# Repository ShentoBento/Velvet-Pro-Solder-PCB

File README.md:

# Velvet Pro Solder PCB

A solder PCB designed to fit the Velvet Pro keyboard by Ampersandy.

Firmware: https://github.com/ShentoBento/Velvet-Pro-PCB-Firmware

---

## Specs

- Solder
- MCU: STM32F072CBTx
- JST SH 4-pin connector (for C3 Unified Daughterboards)
- Fixed ANSI enter
- Fixed 7u bottom row
- Fixed split right shift
- Stepped or full caps lock
- Split or full backspace
- VIA and Vial compatible (via the firmware linked above)

---

## Requirements

- **KiCad 10** or newer. Earlier versions will not open these files.
- Nothing else. All symbols, footprints, and 3D models used by this project are
  included in this repo — no external libraries to install, no PCM packages,
  no library paths to configure.

---

## Opening the project

1. Clone or download this repo.
2. Open `VP_Solder_KiCad/VP_Solder.kicad_pro` in KiCad.

The library paths are stored relative to the project folder, so the repo works
from any location on any operating system. If KiCad reports missing symbols or
footprints, the most likely cause is that the `shentobento_kicad_library/`
folder was not cloned alongside `VP_Solder_KiCad/`.

---

## What's in this repo

### `VP_Solder_KiCad/`

The KiCad project. These are the files you edit.

| File | What it is |
|---|---|
| `VP_Solder.kicad_pro` | Project file — **open this one** |
| `VP_Solder.kicad_sch` | Schematic |
| `VP_Solder.kicad_pcb` | Board layout |
| `fp-lib-table`, `sym-lib-table` | Point KiCad at the bundled library |
| `fabrication-toolkit-options.json` | Settings for the JLCPCB fabrication plugin |

### `VP_Solder_KiCad/production/`

Ready-to-order manufacturing files, generated with the JLCPCB Fabrication Toolkit plugin.

| File | Upload it to |
|---|---|
| `VP_Solder.zip` | JLCPCB's gerber upload — this is the board itself |
| `bom.csv` | Assembly service (which parts) |
| `positions.csv` | Assembly service (where they go) |

If you modify the design, **regenerate these** rather than reusing them. Stale
production files that don't match the current board are how wrong PCBs get
manufactured.

### `shentobento_kicad_library/`

Every symbol and footprint this project uses, in one place.

- `shentobento.kicad_sym` — all symbols
- `shentobento.pretty/` — all footprints
- `3dmodels/` — 3D models for the parts that need them

Symbols come with their footprints pre-assigned, so dragging a part into a
schematic gives you a working part with no footprint assignment step.

This folder is self-contained and can be copied into other keyboard projects.

### `reference files and images`

Not needed to build the board — useful if you're modifying the layout.

- `Plate_File_No_Flex_Cuts.dxf` / `Plate_File_with_Flex_Cuts.dxf` — the official
  Velvet Pro plate files, used to align switch and stabilizer positions
- `VP PCB DXF.dxf` — the official board outline, thanks to Andykit
- Various images of the PCB and schematic

---

## Credits and licenses

Keyboard footprints and symbols are derived from
[marbastlib](https://github.com/ebastler/marbastlib) by ebastler, licensed under
CERN-OHL-P v2. See `shentobento_kicad_library/LICENSE-marbastlib.txt`.

Generic footprints (passives, SOT-23, LQFP-48, JST SH, test points) are copied
from the KiCad standard libraries.

Modifications made to third-party files are recorded in
`shentobento_kicad_library/NOTICE.md`.

The Velvet Pro case and plate files are the work of Ampersandy.

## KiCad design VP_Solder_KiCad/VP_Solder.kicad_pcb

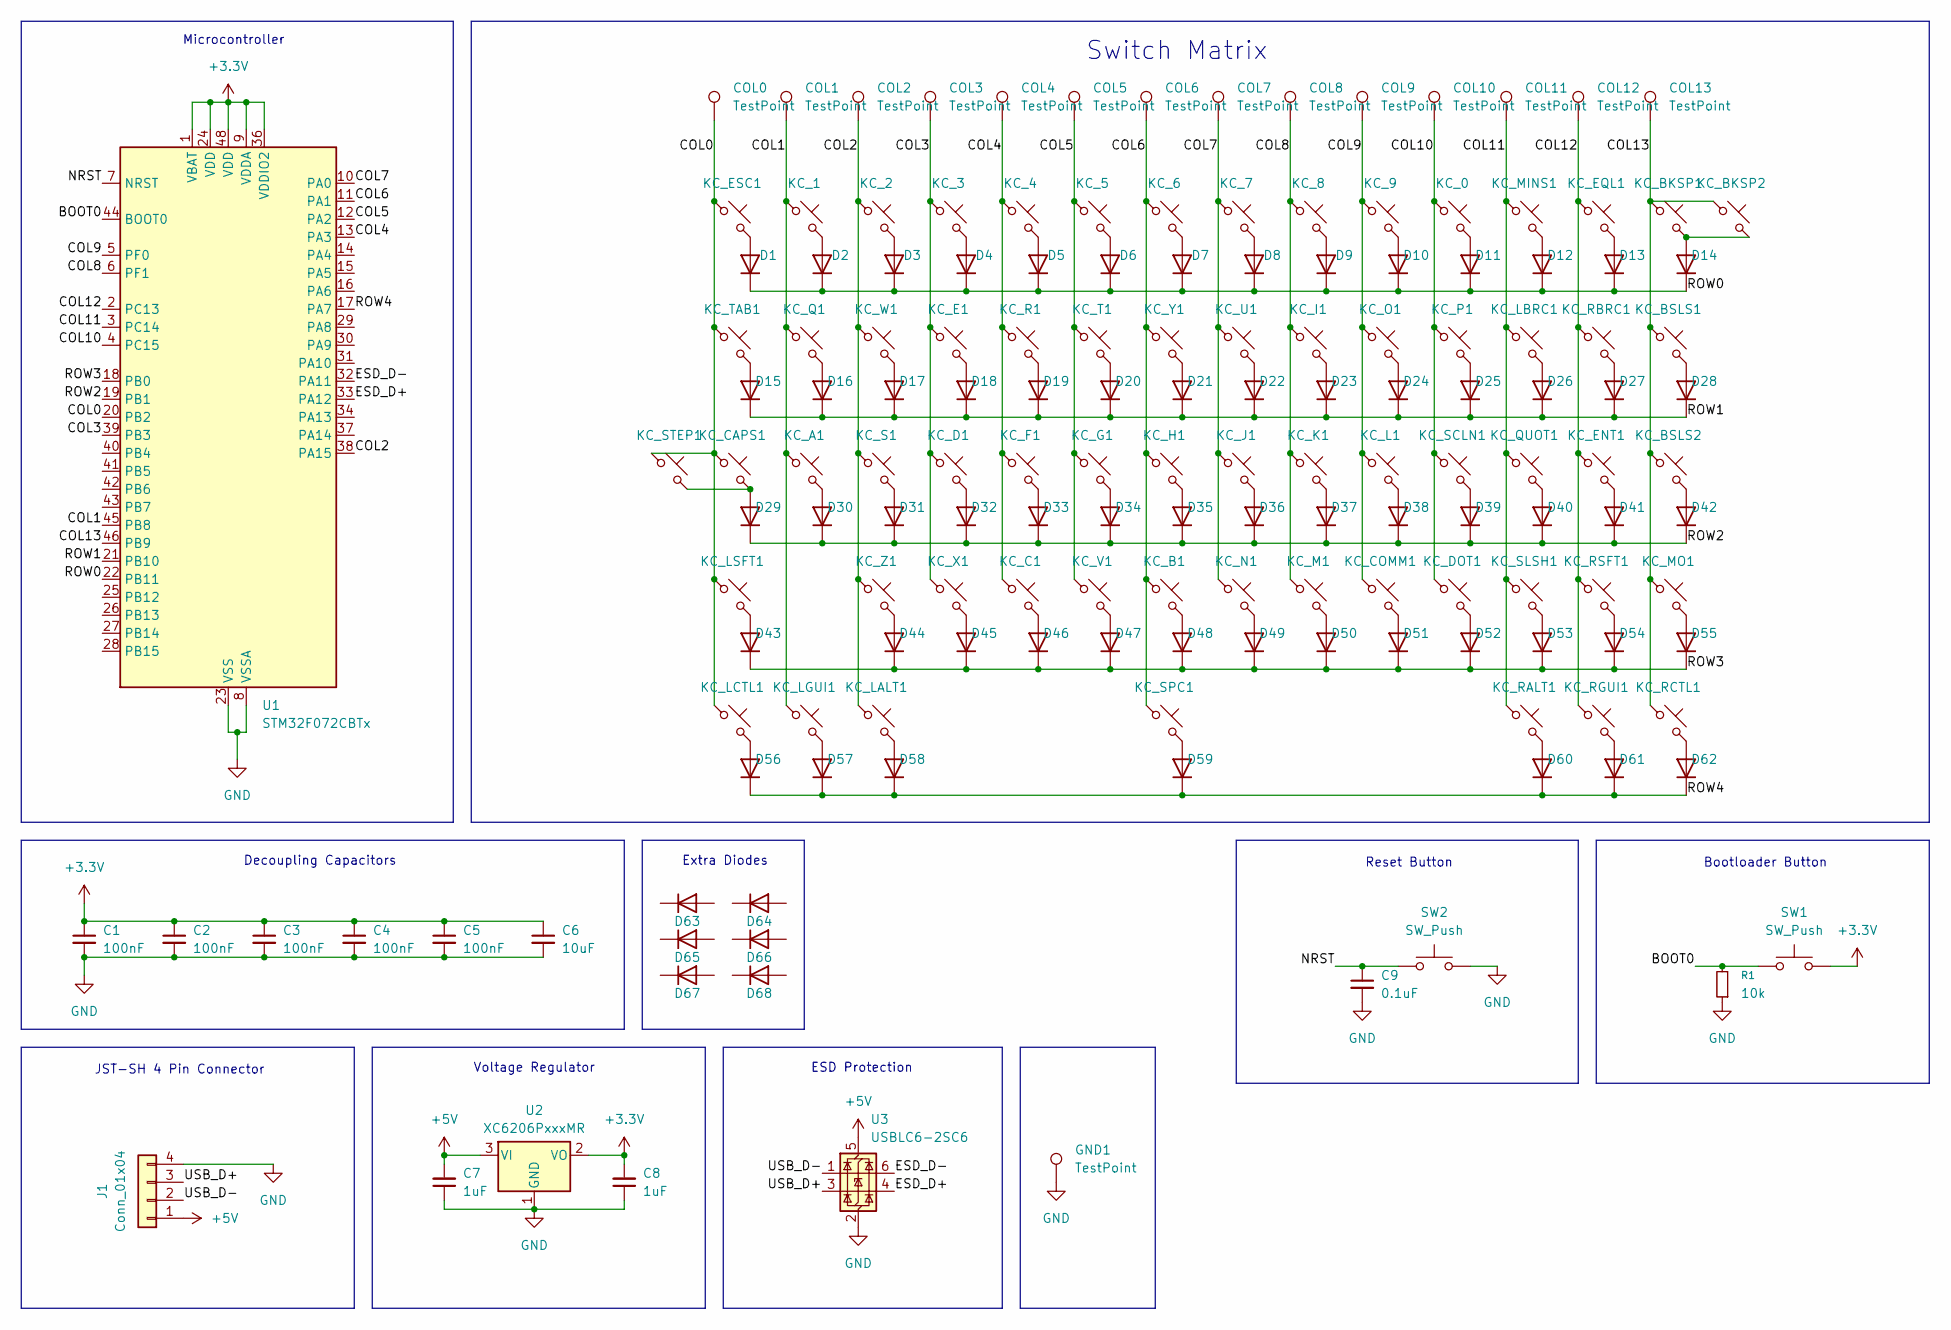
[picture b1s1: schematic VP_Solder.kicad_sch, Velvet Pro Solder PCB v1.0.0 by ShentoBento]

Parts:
C1, C2, C3, C4, C5: 100nF; C_0201_0603Metric
C6: 10uF; C_0805_2012Metric
C7, C8: 1uF; C_0201_0603Metric
C9: 0.1uF; C_0201_0603Metric
COL0, COL1, COL2, COL3, COL4, COL5, COL6, COL7, COL8, COL9, COL10, COL11, COL12, COL13: TestPoint; TestPoint_Pad_1.5x1.5mm
D1, D2, D3, D4, D5, D6, D7, D8, D9, D10, D11, D12, D13, D14, D15, D16, D17, D18, D19, D20, D21, D22, D23, D24, D25, D26, D27, D28, D29, D30, D31, D32, D33, D34, D35, D36, D37, D38, D39, D40, D41, D42, D43, D44, D45, D46, D47, D48, D49, D50, D51, D52, D53, D54, D55, D56, D57, D58, D59, D60, D61, D62, D63, D64, D65, D66, D67, D68: 1N4148; D_SOD-123
GND1: TestPoint; TestPoint_Bridge_Pitch2.0mm_Drill0.7mm
J1: Conn_01x04; JST_SH_1x04
KC_0, KC_1, KC_2, KC_3, KC_4, KC_5, KC_6, KC_7, KC_8, KC_9: MX_SW_solder; SW_MX_1u
KC_A1: MX_SW_solder; SW_MX_1u
KC_B1: MX_SW_solder; SW_MX_1u
KC_BKSP1, KC_BKSP2: MX_SW_solder; SW_MX_1u
KC_BSLS1: MX_SW_solder; SW_MX_1.5u
KC_BSLS2: MX_SW_solder; SW_MX_1u
KC_C1: MX_SW_solder; SW_MX_1u
KC_CAPS1: MX_SW_solder; SW_MX_1.75u
KC_COMM1: MX_SW_solder; SW_MX_1u
KC_D1: MX_SW_solder; SW_MX_1u
KC_DOT1: MX_SW_solder; SW_MX_1u
KC_E1: MX_SW_solder; SW_MX_1u
KC_ENT1: MX_SW_solder; SW_MX_1u
KC_EQL1: MX_SW_solder; SW_MX_1u
KC_ESC1: MX_SW_solder; SW_MX_1u
KC_F1: MX_SW_solder; SW_MX_1u
KC_G1: MX_SW_solder; SW_MX_1u
KC_H1: MX_SW_solder; SW_MX_1u
KC_I1: MX_SW_solder; SW_MX_1u
KC_J1: MX_SW_solder; SW_MX_1u
KC_K1: MX_SW_solder; SW_MX_1u
KC_L1: MX_SW_solder; SW_MX_1u
KC_LALT1: MX_SW_solder; SW_MX_1.5u
KC_LBRC1: MX_SW_solder; SW_MX_1u
KC_LCTL1: MX_SW_solder; SW_MX_1.5u
KC_LGUI1: MX_SW_solder; SW_MX_1u
KC_LSFT1: MX_SW_solder; SW_MX_1u
KC_M1: MX_SW_solder; SW_MX_1u
KC_MINS1: MX_SW_solder; SW_MX_1u
KC_MO1: MX_SW_solder; SW_MX_1u
KC_N1: MX_SW_solder; SW_MX_1u
KC_O1: MX_SW_solder; SW_MX_1u
KC_P1: MX_SW_solder; SW_MX_1u
KC_Q1: MX_SW_solder; SW_MX_1u
KC_QUOT1: MX_SW_solder; SW_MX_1u
KC_R1: MX_SW_solder; SW_MX_1u
KC_RALT1: MX_SW_solder; SW_MX_1.5u
KC_RBRC1: MX_SW_solder; SW_MX_1u
KC_RCTL1: MX_SW_solder; SW_MX_1.5u
KC_RGUI1: MX_SW_solder; SW_MX_1u
KC_RSFT1: MX_SW_solder; SW_MX_1u
KC_S1: MX_SW_solder; SW_MX_1u
KC_SCLN1: MX_SW_solder; SW_MX_1u
KC_SLSH1: MX_SW_solder; SW_MX_1u
KC_SPC1: MX_SW_solder; SW_MX_1u
KC_STEP1: MX_SW_solder; SW_MX_1.75u_STEPPED_1.25
KC_T1: MX_SW_solder; SW_MX_1u
KC_TAB1: MX_SW_solder; SW_MX_1.5u
KC_U1: MX_SW_solder; SW_MX_1u
KC_V1: MX_SW_solder; SW_MX_1u
KC_W1: MX_SW_solder; SW_MX_1u
KC_X1: MX_SW_solder; SW_MX_1u
KC_Y1: MX_SW_solder; SW_MX_1u
KC_Z1: MX_SW_solder; SW_MX_1u
R1: 10k; R_0201_0603Metric
SW1, SW2: SW_Push; SW_Push_Reset_Bootloader
U1: STM32F072CBTx; MCU_STM32F072CBTx
U2: XC6206PxxxMR; SOT-23-3
U3: USBLC6-2SC6; SOT-23-6

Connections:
+3.3V: C1.1, C2.1, C3.1, C4.1, C5.1, C6.1, C8.2, SW1.2, U1.1 (VBAT), U1.9 (VDDA), U1.24 (VDD), U1.36 (VDDIO2), U1.48 (VDD), U2.2 (VO)
+5V: C7.2, J1.1, U2.3 (VI), U3.5 (VBUS)
/BOOT0: R1.2, SW1.1, U1.44 (BOOT0)
/COL0: COL0.1 (1_1), KC_CAPS1.1, KC_ESC1.1, KC_LCTL1.1, KC_LSFT1.1, KC_STEP1.1, KC_TAB1.1, U1.20 (PB2)
/COL1: COL1.1 (1_1), KC_1.1, KC_A1.1, KC_LGUI1.1, KC_Q1.1, U1.45 (PB8)
/COL2: COL2.1 (1_1), KC_2.1, KC_LALT1.1, KC_S1.1, KC_W1.1, KC_Z1.1, U1.38 (PA15)
/COL3: COL3.1 (1_1), KC_3.1, KC_D1.1, KC_E1.1, KC_X1.1, U1.39 (PB3)
/COL4: COL4.1 (1_1), KC_4.1, KC_C1.1, KC_F1.1, KC_R1.1, U1.13 (PA3)
/COL5: COL5.1 (1_1), KC_5.1, KC_G1.1, KC_T1.1, KC_V1.1, U1.12 (PA2)
/COL6: COL6.1 (1_1), KC_6.1, KC_B1.1, KC_H1.1, KC_SPC1.1, KC_Y1.1, U1.11 (PA1)
/COL7: COL7.1 (1_1), KC_7.1, KC_J1.1, KC_N1.1, KC_U1.1, U1.10 (PA0)
/COL8: COL8.1 (1_1), KC_8.1, KC_I1.1, KC_K1.1, KC_M1.1, U1.6 (PF1)
/COL9: COL9.1 (1_1), KC_9.1, KC_COMM1.1, KC_L1.1, KC_O1.1, U1.5 (PF0)
/COL10: COL10.1 (1_1), KC_0.1, KC_DOT1.1, KC_P1.1, KC_SCLN1.1, U1.4 (PC15)
/COL11: COL11.1 (1_1), KC_LBRC1.1, KC_MINS1.1, KC_QUOT1.1, KC_RALT1.1, KC_SLSH1.1, U1.3 (PC14)
/COL12: COL12.1 (1_1), KC_ENT1.1, KC_EQL1.1, KC_RBRC1.1, KC_RGUI1.1, KC_RSFT1.1, U1.2 (PC13)
/COL13: COL13.1 (1_1), KC_BKSP1.1, KC_BKSP2.1, KC_BSLS1.1, KC_BSLS2.1, KC_MO1.1, KC_RCTL1.1, U1.46 (PB9)
/ESD_D+: U1.33 (PA12), U3.4 (I/O2)
/ESD_D-: U1.32 (PA11), U3.6 (I/O1)
/NRST: C9.1, SW2.1, U1.7 (NRST)
/ROW0: D1.1 (K), D2.1 (K), D3.1 (K), D4.1 (K), D5.1 (K), D6.1 (K), D7.1 (K), D8.1 (K), D9.1 (K), D10.1 (K), D11.1 (K), D12.1 (K), D13.1 (K), D14.1 (K), U1.22 (PB11)
/ROW1: D15.1 (K), D16.1 (K), D17.1 (K), D18.1 (K), D19.1 (K), D20.1 (K), D21.1 (K), D22.1 (K), D23.1 (K), D24.1 (K), D25.1 (K), D26.1 (K), D27.1 (K), D28.1 (K), U1.21 (PB10)
/ROW2: D29.1 (K), D30.1 (K), D31.1 (K), D32.1 (K), D33.1 (K), D34.1 (K), D35.1 (K), D36.1 (K), D37.1 (K), D38.1 (K), D39.1 (K), D40.1 (K), D41.1 (K), D42.1 (K), U1.19 (PB1)
/ROW3: D43.1 (K), D44.1 (K), D45.1 (K), D46.1 (K), D47.1 (K), D48.1 (K), D49.1 (K), D50.1 (K), D51.1 (K), D52.1 (K), D53.1 (K), D54.1 (K), D55.1 (K), U1.18 (PB0)
/ROW4: D56.1 (K), D57.1 (K), D58.1 (K), D59.1 (K), D60.1 (K), D61.1 (K), D62.1 (K), U1.17 (PA7)
/USB_D+: J1.3, U3.3 (I/O2)
/USB_D-: J1.2, U3.1 (I/O1)
GND: C1.2, C2.2, C3.2, C4.2, C5.2, C6.2, C7.1, C8.1, C9.2, GND1.1 (1_1), J1.4, R1.1, SW2.2, U1.8 (VSSA), U1.23 (VSS), U1.35 (VSS), U1.47 (VSS), U2.1 (GND), U3.2 (GND)
unnamed: D1.2 (A), KC_ESC1.2
unnamed: D2.2 (A), KC_1.2
unnamed: D3.2 (A), KC_2.2
unnamed: D4.2 (A), KC_3.2
unnamed: D5.2 (A), KC_4.2
unnamed: D6.2 (A), KC_5.2
unnamed: D7.2 (A), KC_6.2
unnamed: D8.2 (A), KC_7.2
unnamed: D9.2 (A), KC_8.2
unnamed: D10.2 (A), KC_9.2
unnamed: D11.2 (A), KC_0.2
unnamed: D12.2 (A), KC_MINS1.2
unnamed: D13.2 (A), KC_EQL1.2
unnamed: D14.2 (A), KC_BKSP1.2, KC_BKSP2.2
unnamed: D15.2 (A), KC_TAB1.2
unnamed: D16.2 (A), KC_Q1.2
unnamed: D17.2 (A), KC_W1.2
unnamed: D18.2 (A), KC_E1.2
unnamed: D19.2 (A), KC_R1.2
unnamed: D20.2 (A), KC_T1.2
unnamed: D21.2 (A), KC_Y1.2
unnamed: D22.2 (A), KC_U1.2
unnamed: D23.2 (A), KC_I1.2
unnamed: D24.2 (A), KC_O1.2
unnamed: D25.2 (A), KC_P1.2
unnamed: D26.2 (A), KC_LBRC1.2
unnamed: D27.2 (A), KC_RBRC1.2
unnamed: D28.2 (A), KC_BSLS1.2
unnamed: D29.2 (A), KC_CAPS1.2, KC_STEP1.2
unnamed: D30.2 (A), KC_A1.2
unnamed: D31.2 (A), KC_S1.2
unnamed: D32.2 (A), KC_D1.2
unnamed: D33.2 (A), KC_F1.2
unnamed: D34.2 (A), KC_G1.2
unnamed: D35.2 (A), KC_H1.2
unnamed: D36.2 (A), KC_J1.2
unnamed: D37.2 (A), KC_K1.2
unnamed: D38.2 (A), KC_L1.2
unnamed: D39.2 (A), KC_SCLN1.2
unnamed: D40.2 (A), KC_QUOT1.2
unnamed: D41.2 (A), KC_ENT1.2
unnamed: D42.2 (A), KC_BSLS2.2
unnamed: D43.2 (A), KC_LSFT1.2
unnamed: D44.2 (A), KC_Z1.2
unnamed: D45.2 (A), KC_X1.2
unnamed: D46.2 (A), KC_C1.2
unnamed: D47.2 (A), KC_V1.2
unnamed: D48.2 (A), KC_B1.2
unnamed: D49.2 (A), KC_N1.2
unnamed: D50.2 (A), KC_M1.2
unnamed: D51.2 (A), KC_COMM1.2
unnamed: D52.2 (A), KC_DOT1.2
unnamed: D53.2 (A), KC_SLSH1.2
unnamed: D54.2 (A), KC_RSFT1.2
unnamed: D55.2 (A), KC_MO1.2
unnamed: D56.2 (A), KC_LCTL1.2
unnamed: D57.2 (A), KC_LGUI1.2
unnamed: D58.2 (A), KC_LALT1.2
unnamed: D59.2 (A), KC_SPC1.2
unnamed: D60.2 (A), KC_RALT1.2
unnamed: D61.2 (A), KC_RGUI1.2
unnamed: D62.2 (A), KC_RCTL1.2

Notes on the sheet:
Reset Button
Microcontroller
Voltage Regulator
Extra Diodes
JST-SH 4 Pin Connector
Bootloader Button
ESD Protection
Decoupling Capacitors
Switch Matrix

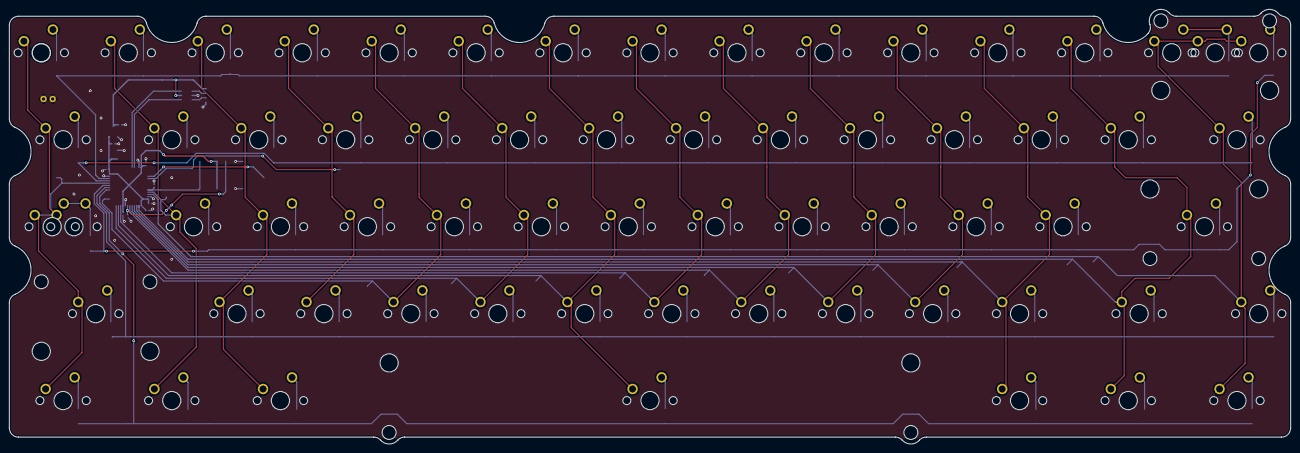
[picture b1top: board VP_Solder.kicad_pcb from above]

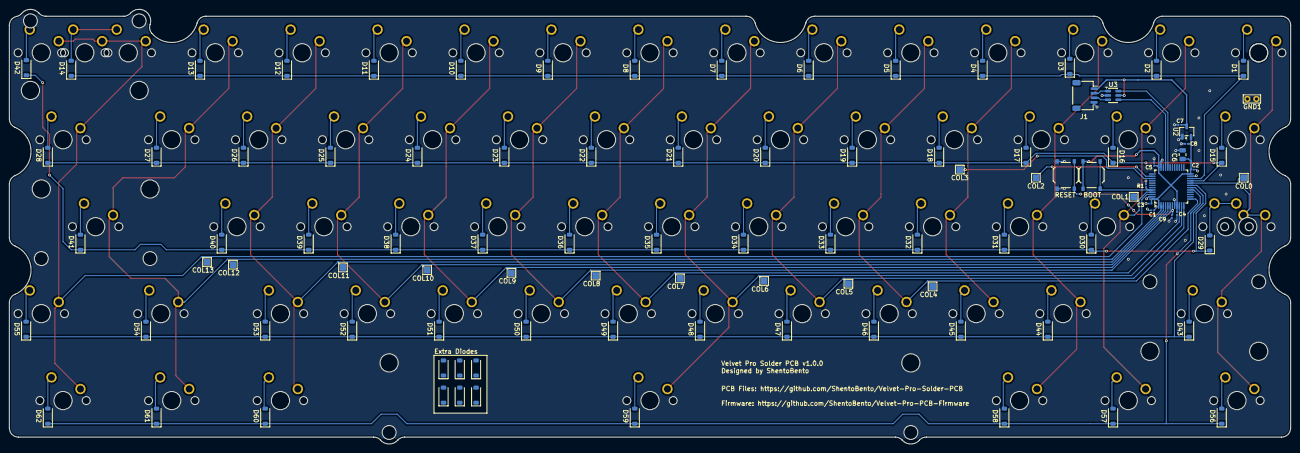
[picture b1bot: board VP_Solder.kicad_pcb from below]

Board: 2 copper layers, 280.7 x 95.2 mm, 163 parts (99 on the bottom side), 90 nets.

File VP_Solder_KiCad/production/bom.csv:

Designator,Footprint,Quantity,Value,LCSC Part #
"C1, C2, C3, C4, C5",0201,5,100nF,
C6,0805,1,10uF,
"C7, C8",0201,2,1uF,
C9,0201,1,0.1uF,
"COL0, COL1, COL10, COL11, COL12, COL13, COL2, COL3, COL4, COL5, COL6, COL7, COL8, COL9",TestPoint_Pad_1.5x1.5mm,14,TestPoint,
"D1, D10, D11, D12, D13, D14, D15, D16, D17, D18, D19, D2, D20, D21, D22, D23, D24, D25, D26, D27, D28, D29, D3, D30, D31, D32, D33, D34, D35, D36, D37, D38, D39, D4, D40, D41, D42, D43, D44, D45, D46, D47, D48, D49, D5, D50, D51, D52, D53, D54, D55, D56, D57, D58, D59, D6, D60, D61, D62, D63, D64, D65, D66, D67, D68, D7, D8, D9",D_SOD-123,68,1N4148,
GND1,TestPoint_Bridge_Pitch2.0mm_Drill0.7mm,1,TestPoint,
J1,JST_SH_1x04,1,Conn_01x04,
"KC_0, KC_1, KC_2, KC_3, KC_4, KC_5, KC_6, KC_7, KC_8, KC_9, KC_A1, KC_B1, KC_BKSP1, KC_BKSP2, KC_BSLS2, KC_C1, KC_COMM1, KC_D1, KC_DOT1, KC_E1, KC_ENT1, KC_EQL1, KC_ESC1, KC_F1, KC_G1, KC_H1, KC_I1, KC_J1, KC_K1, KC_L1, KC_LBRC1, KC_LGUI1, KC_LSFT1, KC_M1, KC_MINS1, KC_MO1, KC_N1, KC_O1, KC_P1, KC_Q1, KC_QUOT1, KC_R1, KC_RBRC1, KC_RGUI1, KC_RSFT1, KC_S1, KC_SCLN1, KC_SLSH1, KC_SPC1, KC_T1, KC_U1, KC_V1, KC_W1, KC_X1, KC_Y1, KC_Z1",SW_MX_1u,56,MX_SW_solder,
"KC_BSLS1, KC_LALT1, KC_LCTL1, KC_RALT1, KC_RCTL1, KC_TAB1",SW_MX_1.5u,6,MX_SW_solder,
KC_CAPS1,SW_MX_1.75u,1,MX_SW_solder,
KC_STEP1,SW_MX_1.75u_STEPPED_1.25,1,MX_SW_solder,
R1,0201,1,10k,
"SW1, SW2",SW_Push_Reset_Bootloader,2,SW_Push,
U1,MCU_STM32F072CBTx,1,STM32F072CBTx,
U2,SOT-23-3,1,XC6206PxxxMR,
U3,SOT-23-6,1,USBLC6-2SC6,

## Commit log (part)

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2026-04-05 Initial KiCad project files
2026-04-05 Add marbastlib external KiCad libraries
2026-04-05 Migrate to KiCad 10 and save symbol library paths
2026-04-05 added microcontroller, decoupling capacitors
2026-04-06 added voltage regulator, jst connector, matrix
    voltage regular and matrix are unfinished
2026-04-06 Visual changes to schematic
2026-04-06 Added USB Resistors, ESD Protection, Reset and bootloader buttons
2026-04-06 Small changes to schematic
2026-04-06 PCB Layout Rough Draft
2026-04-06 Fixed stab keys on pcb
2026-04-06 added vp plate files
2026-04-06 Added row/column traces
2026-04-06 Added Ai03 Library, fixed stab positions
2026-04-06 minor changes
2026-04-06 rearranging pcb
2026-04-07 new traces made
2026-04-09 added velvet pro pcb outline
2026-04-09 added pcb outline to pcb
2026-04-09 Routed traces columns 7-11
2026-04-10 test export fab files
2026-04-12 finished row/column traces
2026-04-12 Rerouted everything
2026-04-12 updated pushbuttons
2026-04-13 idk what i changed here
2026-04-13 added ground plane, completed power traces
    just need bootloader and reset buttons to be routed next, also increase trace width for power cables
2026-04-14 finished wiring everything
    ratsnest gone
2026-04-14 Final changes
2026-04-14 added files to new folder
2026-04-14 Added Production Files
2026-04-14 Rename KiCad project to VP_Solder and clean up production files
2026-04-14 Add initial README with PCB specifications
2026-04-17 Added split backspace
2026-04-17 Added testpoints
2026-04-17 ran drc, fixed some tracing errors
2026-04-17 fixed DRC errors
2026-04-17 Small changes to silkscreen
2026-04-17 Changed testpoint names
2026-04-17 Changed silkscreen
2026-04-17 Clarify backspace and caps lock options in README
    Updated specifications to clarify options for backspace and caps lock.
2026-04-18 final changes, drc fixes
2026-04-18 Cleaup
2026-04-19 Finished
2026-05-14 Add firmware link to README
    Add firmware link to README
